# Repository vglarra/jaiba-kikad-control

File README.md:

# jaiba-kicad-control

KiCad project for the Jaiba hexa-drum's control board: three Teensy 4.1s in
sockets — one per hemisphere plus one for the UI — with a velostat **and** a
piezo front-end for every drum sensor, plus five loop-control sensors.

## System overview

```mermaid
graph LR
    R["Right hemisphere Teensy<br/>9 sensors x (velostat + piezo)<br/>USB-MIDI out"]
    L["Left hemisphere Teensy<br/>7 sensors x (velostat + piezo)<br/>+ 5 loop sensors via mux<br/>USB-MIDI out"]
    UI["UI Teensy<br/>ST7796 TFT + XPT2046 touch"]

    R -- "Serial1, crossed<br/>pins 0/1" --> UI
    L -- "Serial3, crossed<br/>pins 14/15" --> UI
```

Every sensor Teensy sends MIDI straight to the host over its own USB port; the
UART links carry calibration commands and live monitoring only. Each sensor
Teensy is a separate USB-MIDI device and the host merges them.

## The 18-analog-input ceiling

This is the constraint the whole layout follows.

A Teensy 4.1 has exactly **18 analog inputs**, and it is a hardware limit, not a
software one: the i.MX RT1062 has 18 ADC-capable pads and Teensy 4.1 breaks all
of them out. Pins 28–37 are *not* analog — the core's `pin_to_channel[]` table
returns `255` for them, and `analogRead()` returns 0.

```
A0  A1  A2  A3  A4  A5  A6  A7  A8  A9  A10 A11 A12 A13 A14 A15 A16 A17
14  15  16  17  18  19  20  21  22  23  24  25  26  27  38  39  40  41
```

Each drum sensor needs **two** analog inputs — one for its velostat layer, one
for its piezo layer — so:

| Board | Sensors | Analog pins | Spare |
|---|---|---|---|
| Right hemisphere | 9 dual-layer | 18/18 | 0 |
| Left hemisphere | 7 dual-layer + 5 loop | 15/18 | 3 |
| UI Teensy | — | 0/18 | 16 |
| **Total** | **16 dual-layer + 5 loop = 21** | | |

The five loop sensors cannot fit alongside the hemisphere sensors: 16 dual-layer
sensors already consume 32 of the two sensor Teensys' 36 analog pins, and the
left Teensy has only **4** spare — one short of five.

So the loop sensors are wired **velostat-only** (they need one pin each, not
two, because nothing needs their attack velocity) and **share a single ADC pin
through a CD74HC4067 16:1 multiplexer** on the left Teensy: `C0`–`C4` are the
loop sensors, `SIG` goes to one analog pin, `S0`–`S3` to four digital pins, and
`EN` is tied to ground so the mux is always enabled. That leaves **11 mux
channels free** for future pads.

**This costs the percussive pads nothing.** The mux is never in their signal
path — they keep dedicated ADC pins — and because the loop sensors leave the
percussive scan entirely, the fast loop actually gets *shorter* (7 pads instead
of the 9 that two dual-layer loop sensors would have made). The loop sensors can
be read on a slow `millis()` cadence since velostat control does not need a
high sample rate.

### Two more things that shape the layout

**The analog pins are lopsided across the two rows.** Fourteen of the eighteen
sit on ROW1 (pins 14–23 and 38–41); only four (24–27) are on ROW2. That is why
each sensor Teensy's 7 ROW1-only sensors are the ones that get dedicated pins,
and why the loop sensors (which need one pin each, not two) were the ones moved
behind the mux.

**Two ADCs.** Pins 26/27 (A12/A13) and 38/39 (A14/A15) are ADC2-only; the other
fourteen are ADC1. `analogRead()` handles the switching transparently, but it
matters if you ever want simultaneous sampling.

## Floorplan

The drum pad cables arrive at the **right-hand edge** of the board, and the three
Teensys' USB sockets point **left**, so the board splits into two regions:

```
   +----------------------------------------------------------+
   |  U_R  [buttons]                       colA         colB  |
   |  U_L  [buttons]   U_MUX             ||    ||      ||   || |
   |  U_UI [TFT]                         ||    ||      ||   || |
   |                                   (8 dual + 3    (8 dual +|
   |                                    loop rows)    2 loops) |
   +----------------------------------------------------------+
```

* **Left** — the three Teensys stacked vertically with their USB sockets facing
  left, each sensor Teensy with its cal/curve buttons below it, plus the mux and
  the TFT header.
* **Right** — every sensor connector, in **two columns of cells whose connectors
  face outward**: 21 connectors at x = 120 mm (11 of them) and x = 152 mm (10).
  The aisle between the columns is what lets a cable reach the inner one.
* **Buses** run vertically at x = 92 mm (3V3) and x = 100 mm (GND), between the
  two regions, where they clear every courtyard on both sides.

A cell's connector sits on the **right** of the cell, which is why
`sensor_cell(..., mirrored=True)` exists: it is a true mirror of the left-facing
variant about the cell's centre line, and mirroring is what keeps the internal
routing crossing-free.

**What this costs.** Gathering the connectors here makes each cell's two runs to
its Teensy long jumpers — roughly 30–130 mm instead of the ~15 mm they were when
the cells sat directly above ROW1. They are wire jumpers either way on a
single-sided board, but it is the main trade of this arrangement: the piezo ADC
node (about 5 kΩ source impedance) now travels the length of the board. If that
shows up as noise on the piezo channels, the fix is to keep the piezo front end
by the Teensy and move only the connector out to the edge.

## Board geometry

* **150 × 260 mm**, two copper layers in KiCad's stackup. Fixed by the enclosure,
  so it is a constraint rather than an outcome. Reaching 150 wide was a re-flow
  of the left region, not of the cell columns: the old layout had ~30 mm of dead
  space between the Teensys and the buses. The extra 20 mm of height went into
  the cell row pitch (25 → 27 mm) and the button cluster.
* Rows are **15.24 mm apart** (0.6"), pin span 58.42 mm, board 60.96 × 17.78 mm.
  (0.7" is the *board width*, not the row pitch — an earlier revision used
  17.78 mm as `ROW_GAP` and the sockets could not line up with a real Teensy.)
* Power buses run the full height at x = 66 mm (3V3) and x = 71 mm (GND).
  Neither bar is tapped by any track or pad — they are hand-soldered jumper
  rails, and the ground connection is the F.Cu pour. The channel they sit in is
  bounded by the wire-pad fan at x = 64.81 on the left and the sensor front-ends
  at 78.79 on the right, so a future move anywhere in 73–78 is clear.
* Mounting holes at 6 mm in from each corner.

## Sensor front-ends

Each sensor is one 4-pin connector (`3V3`, `VELO`, `PIEZO`, `GND`) plus its
divider parts, so a hemisphere's nine sensors are nine identical cells:

**Velostat layer** — the sheet is the top leg, the board's 100 Ω is the bottom:

```
3V3 ── velostat ──┬── VELO  (ADC pin)
                  │
                 100Ω
                  │
                 GND
```

**Piezo layer** — 10k/10k attenuator with a clamp diode:

```
PIEZO ── R1 (10k) ──┬── PSIG  (ADC pin)
                    │
                   R2 (10k)          1N4148
                    │                 │
                   GND      anode ────┴──── cathode → 3V3
```

The diode's **anode** faces the ADC node and its **cathode** faces 3.3 V. Note
that KiCad's `D_DO-35_SOD27_P7.62mm_Horizontal` numbers pad 1 as the *cathode*
— the earlier revision of this board had pad 1 on the ADC node, which
forward-biases the diode for any signal below ~2.6 V and clamps the piezo node
flat instead of protecting it.

## Pin tables (verified)

Read off a real Teensy 4.1, then cross-checked against a published Teensy 4.1
footprint and symbol pair (the two agree exactly). Index 0 is the end nearest
the USB connector.

```
ROW1: 5V, GND, 3V3, 23, 22, 21, 20, 19, 18, 17, 16, 15, 14, 13, GND, 41, 40, 39, 38, 37, 36, 35, 34, 33
ROW2: GND, 0, 1, 2, 3, 4, 5, 6, 7, 8, 9, 10, 11, 12, 3V3, 24, 25, 26, 27, 28, 29, 30, 31, 32
```

The 5 V pin is the pin PJRC calls VIN; there is no VIN pad in either main row.

### Copper sizes for home etching

This board is hand-etched — no solder mask, no plated barrels — so the copper is
deliberately far fatter than a fab would ask for. Three constants in
`jaiba_board_layout.py` drive it, and all three footprint generators read them,
so changing them keeps the library and the board in step:

```python
TRACK_W = 0.8          # signal
BUS_W   = 1.0          # power bus bar
PAD_DIA = 2.2          # every plated through-hole pad
```

What that produces on the finished board:

| feature | size |
|---|---|
| pad diameter, all plated pads | 2.2 mm |
| track width | 0.8 mm signal, 1.0 mm bus |
| **narrowest gap, pad to pad** | **0.34 mm** |
| narrowest gap, track to pad | 1.04 mm |
| narrowest gap, track to track | 1.74 mm |
| smallest annular ring | 0.55 mm |
| mounting holes | 3.2 mm NPTH, unplated (unchanged) |

**The 0.34 mm pad-to-pad gap is the etch limit.** It is not a one-off: it occurs
at every adjacent pair on every 2.54 mm header, which is most of the board. Two
2.2 mm pads on a 2.54 mm grid leave 2.54 − 2.2 = 0.34 mm, and at that pitch **no
track can pass between two pads at all** (2.54 − 2.2 − 0.8 < 0) — which is why
the cell routing goes around pads rather than between them.

That gap is comfortable for toner transfer *if* the toner adheres and you do not
over-etch; it is where a home board will bridge first if anything does. If it
does, change `PAD_DIA` and re-run the three footprint generators:

| `PAD_DIA` | pad-to-pad gap |
|---|---|
| 2.2 mm (current) | 0.34 mm |
| 2.0 mm | 0.54 mm |
| 1.8 mm | 0.74 mm |

The board outline and every part position are unaffected — only the pads change.

### Single-sided copper

The physical build is one copper layer, so nothing can cross anything else in
copper. KiCad has no single-layer stackup (it requires an even count, minimum
two), so the board is 2-layer in KiCad and single-sided is a *manufacturing*
decision: only `F.Cu` is fabricated, and everything the plan lists as a jumper
becomes an insulated wire on the component side.

The generator draws only what can never cross: the bus bars, the short
intra-cell links, the five loop-sensor wipers, and the seven TFT/touch signals
that run straight up from their header to the UI Teensy's ROW2. **57 jumper
links remain** — each channel's runs to its analog pin, every cell's 3V3/GND
taps, the buttons, the UART links, TFT SCK, and the mux's own power and signal
runs. Run **Inspect → DRC** to see them as ratsnest.

## Files

| Path | What it is |
|---|---|
| `jaiba_board_layout.py` | **Source of truth.** Pure-Python placement + net plan, no `pcbnew`. |
| `jaiba-kicad-controlboard.py` | Applies the plan via `pcbnew`; run inside KiCad's Scripting Console. |
| `kicad-control-board/jaiba.pretty/` | Project-local footprint library — self-contained, no KiCad system libs. |
| `kicad-control-board/*.kicad_pcb` | Generated board (150 × 260 mm, 281 footprints, 612 pads). |
| `tools/make_library.py` | Rebuilds `jaiba.pretty/` by lifting footprints out of the board. |
| `tools/make_teensy_footprint.py` | Generates `Teensy_4.1.kicad_mod` from PJRC's published dimensions. |
| `tools/make_module_footprint.py` | Generates `CD74HC4067_Module.kicad_mod` from caliper measurements, plus its 1:1 check sheet. |
| `tools/make_calibration_sheet.py` | Emits `calibration_1to1.svg` — the ruler that proves a print really is 1:1. |
| `tools/make_teensy_fit_gauge.py` | Emits `teensy_fit_gauge.svg` — nominal Teensy pin rows to lay the real part on. |
| `tools/emit_board.py` | Writes the `.kicad_pcb` from the plan **without** KiCad. |
| `tools/route_jumpers.py` | Pre-routes the wire jumpers onto B.Cu as a guide (see below). |
| `tools/check_pour.py` | Measures whether a ground pour would actually connect (see below). |
| `tools/preview_board.py` | Renders the board to an SVG so a floorplan change can be eyeballed without KiCad. |
| `tools/verify_board.py` | DRC-style geometry checker (plan or emitted board). |
| `tools/kicad_sexpr.py` | S-expression reader/writer, quote-preserving. |

## Regenerating the board

**With KiCad** — open the PCB Editor, open **Tools → Scripting Console**:

```python
exec(open(r'/path/to/jaiba-kicad-controlboard.py').read())
```

**Without KiCad** — the same board straight from the plan:

```bash
python3 tools/emit_board.py            # writes kicad-control-board.kicad_pcb
python3 tools/verify_board.py kicad-control-board/kicad-control-board.kicad_pcb
```

**Full rebuild from scratch** — if `jaiba.pretty/` is ever missing, this
regenerates every footprint before the board. Order matters: the library has to
exist before `emit_board.py` can read it.

```bash
python3 tools/make_library.py           # passives, lifted out of the board
python3 tools/make_teensy_footprint.py  # Teensy 4.1, from PJRC dimensions
python3 tools/make_module_footprint.py  # CD74HC4067 module, from caliper measurements
python3 tools/emit_board.py
python3 tools/route_jumpers.py          # optional: B.Cu jumper guide
python3 tools/verify_board.py kicad-control-board/kicad-control-board.kicad_pcb
```

`verify_board.py` checks that no pad or courtyard leaves the outline, no two
pads overlap, no courtyards collide, and no track breaks clearance from another
net, a pad, or a mounting hole. A clean run prints `RESULT: clean`.

**Footprint library.** `jaiba.pretty/` is committed and self-contained, so
neither route needs KiCad's system libraries or a configured install path.
`make_library.py` only needs re-running if you change the passives; it lifts
their geometry out of a board that KiCad wrote. `make_teensy_footprint.py`
generates the Teensy footprint from PJRC's published dimensions, and
`make_module_footprint.py` generates the mux module footprint from your caliper
measurements — it prints a 1:1 SVG sheet alongside, for checking against the
real board on paper.

**Format version.** The emitted board declares KiCad 9's format
(`20241229`). KiCad 9 and 10 both open it; a newer KiCad will offer to upgrade
it in place. The stackup, design rules and plot parameters in
`tools/emit_board.py`'s `BOARD_TEMPLATE` are captured verbatim from a
KiCad-written board — edit them there rather than by hand in the `.kicad_pcb`,
which is regenerated.

## Drum-cable solder pads

The drum cable takes all the movement, so each of its four lands on its own bare
copper pad rather than only on a 2.2 mm through-hole pad. **74 pads** — four per
dual-layer cell (3V3, VELO, PRAW, GND) and two per loop cell.

They are `SolderPad_1x01`: an **8.0 × 2.0 mm rectangle of exposed copper**
(`F.Cu` + `F.Mask` only — no paste layer, because there is no stencil), sitting
just outboard of each cell's connector and fed by a straight horizontal stub
from its pin. Per connection that is 3.8 mm² of through-hole pad plus 16.0 mm² of
rectangle — **19.8 mm², 5.2× the round pad alone** — and an **8 mm run of copper**
to solder the wire along rather than one small pad.

Two constraints shaped it:

* **They could not go beside the connector in X.** The passives are ~1 mm to its
  left and the cell edge 0.8 mm to its right, so every vertical channel inside
  the cell is blocked. Outboard of the connector is the only clear space — which
  also happens to be the side the drum cable arrives from.
* **2.0 mm tall, not more.** Adjacent pins are 2.54 mm apart, so the height is
  capped at ~2.34 mm before neighbouring courtyards touch. The 2.4 mm courtyard
  leaves 0.14 mm between them.
* **8 mm is the length limit in practice** — and only because of where the pads
  land, not a rule. At 8 mm the rightmost pad ends 9.5 mm short of the edge.

Being surface-mount, these add **no holes** — the drill count is unchanged.

The 8 mm length pushed the loop cells' jumper pads out of the strip they shared
with the drum pads, so those moved below (row pitch 8 → 11 mm) and column B moved
110 → 114 mm to keep the aisle between the columns. The left region absorbed the
rest of the squeeze to 150 mm wide, leaving both cell columns where they are.

## Wire landing pads

Soldering a jumper onto a pin that already holds a socket or a module pin puts
**two joints in one hole** and pours heat into the part. So every end of every
jumper gets a pad of its own, reached by a short F.Cu stub. **100 of them:**

| where | pads | why |
|---|---|---|
| beside the Teensys | 50 | 22 right, 23 left (it also carries the mux lines), 5 UI |
| beside the mux module | 13 | `C0`–`C4`, `SIG`, `S0`–`S3`, `EN`, `VCC`, `GND` |
| in the sensor cells | 32 | `VELO` and `PSIG` for each of the 16 dual-layer sensors |
| in the loop cells | 5 | `VELO` for each |

TFT pins 6–12 have none: they are already drawn in copper to the header.

**Beside the Teensys and the mux** the pads step *diagonally* — each one further
out from the pin row and further along than the last — so the wires comb out
instead of bunching at 2.54 mm pitch. Stubs cannot cross, provably: a stub always
ends left of where the next one starts (`i × 1.15 < 2.54 × (i+1)`). Consecutive
pads land about 3.9 mm apart. The mux's channel inputs fan up and its control
pins fan down, so the module's two rows don't fight for the same space.

**In the sensor cells** the two pads go on the sides their nodes already live on,
because putting both on the right makes the two routes *topologically cross* —
no planar routing can fix that:

```
        R_VELO                                          J_PAD  (3V3 VELO PRAW GND)
   ┌──────────────┐                                        │
   │   ○ VELO     │  <- velostat pad, in the free band      │
   ├──────────────┤     between R_VELO and R1               │
   │   R1    R2   │                                         │
   │              │                                         │
   │   D          │  ○ PSIG  <- piezo pad, crossed on y=18.5 │
   └──────────────┘
```

The cal/curve buttons moved to the right-hand side of each Teensy for this: their
pads were landing *inside* the switches. Being off to the side also puts them
somewhere a finger can reach.

The B.Cu jumper guide aims at these pads rather than at component leads, which is
where the wire physically goes.

## The B.Cu jumper guide

The board is single-sided, so the ~60 connections the generator leaves unrouted
become insulated wire jumpers on the component side. KiCad draws those as
straight ratsnest lines, which at this count is an unreadable spider web.

`tools/route_jumpers.py` lays a plausible *path* for each one on **B.Cu**. That
layer is not fabricated, so it is free to use as a map, and it is a faithful
model:

* every jumper ends on a through-hole pad, and THT pads exist on all copper
  layers, so **no vias are ever needed**;
* a B.Cu track cannot clash with the F.Cu copper — which is exactly right, since
  the real wires are insulated and cross traces freely;
* B.Cu coordinates map 1:1 onto the component side, so what you see in the normal
  top view is where the wire physically goes.

Routes are orthogonal paths on a 0.635 mm lattice, avoiding pads of other nets,
mounting holes and the board edge. **They are allowed to cross each other** —
forbidding that is not a real constraint for insulated wire, and enforcing it
strangled the few corridors into the Teensys. So the guide contains many
crossings on purpose.

> **When plotting for etching, select `F.Cu` only.** B.Cu now contains copper and
> must never be made. `kicad-cli pcb export gerbers` would export both.

The verifier knows about layers: it checks F.Cu strictly, and reports B.Cu
crossings as a count rather than as shorts. KiCad's own DRC will flag them —
exclude B.Cu, or just remember what that layer is.

## A note on file formatting

`emit_board.py` refuses to write a board whose quoting KiCad would reject. The
specific trap: KiCad's parser accepts a bare *symbol* almost anywhere — unquoted
`(layer F.Cu)` and bare uuids load fine — but a value that tokenises as a
**number** where it wants a symbol is fatal. `(generator_version 9.0)` produces
exactly one error, naming a line number and nothing else:

```
Expecting 'symbol' in '...kicad-control-board.kicad_pcb', line 27117, offset 22
```

The lint walks the tree before writing and reports the path to any such value,
so this surfaces as a build error instead of a KiCad load failure.

Worth knowing: `make_library.py` lifts the passive footprints **out of the
generated board**, so its formatting style feeds back into the library and then
into the next generation. That is self-correcting now that the emitter writes
canonically, but if the board file is ever hand-edited into a non-canonical
style, re-running the chain will propagate it.

## Encoder expansion headers

The UI Teensy has **26 free digital pins** broken out on three headers, so a knob
panel can be added without soldering onto a socket pin:

| | pins | carries |
|---|---|---|
| `J_ENC_A` | 10 | **GND, 3V3**, then Teensy 23, 22, 21, 20, 19, 18, 17, 16 |
| `J_ENC_B` | 9 | Teensy 41, 40, 39, 38, 37, 36, 35, 34, 33 |
| `J_ENC_C` | 9 | Teensy 24, 25, 26, 27, 28, 29, 30, 31, 32 |

All 16 analog-capable pins (16–27, 38–41) are included, plus 10 digital-only ones.
`J_ENC_A` carries the power, taken from the Teensy's own ROW1 GND and 3V3 pins, so
no bus has to be tapped — the encoder commons can share its GND.

**Why three headers and not one.** Each Teensy pin row is a wall: a track cannot
pass between two 2.2 mm pads on a 2.54 mm pitch, so nothing can reach ROW1 from
below. Each header therefore sits on the side of the row it serves, directly
above or below it, and **every trace is a straight vertical** — pin for pin, no
crossings, no jumpers, no vias.

`J_ENC_A` sits 5.5 mm higher than `J_ENC_B` to squeeze between two obstacles: the
mux's channel extension pads below it and the UART landing pad for pin 15 above.
The header courtyard is ±1.77 (it inherits the 1×02 shell), which is what makes
that window so narrow.

### If you use potentiometers instead

Encoders are digital and use no ADC. If you switch to pots, the same headers work
— each pot wiper goes to one pin, 3V3 and GND come from `J_ENC_A`. **16 of the 26
pins are analog-capable**, so there is no need for another multiplexer: the left
Teensy's CD74HC4067 also still has **11 spare channels**, read over the UART.

## The electrostatic shield

The copper fill on F.Cu is tied to **GND** and acts as a coplanar shield and
guard around the high-impedance piezo nodes.

**It has to be grounded.** Floating copper is the opposite of a shield: it
re-radiates and capacitively couples noise onto the very nodes it sits beside.
So the zone carries the ground net and no fragment may be left floating —
`island_removal_mode 2` makes KiCad drop any that reaches no ground pad.

The fragmentation that rules the fill out as a ground *return path* is fine for
a shield, because each piece only has to be grounded, not joined to the others:

```
SHIELD : 15 of 146 pour regions reach ground
         292.81 cm2 of useful shield      (75% of the board)
         4.52 cm2 floating -> removed     (1.2%, negligible)
```

Ground reaches each region through a thermal spoke from a ground pad, and those
pads are being wired anyway — so the shield needs no extra connections. It also
does some of that wiring for you: with the shield, ground forms 15 groups instead
of 31, so relying on it would cut the ground wires from 31 to about 14. That is
still the unpredictable road, so the board is built for the 31.

Roughly three quarters of the board is also bare laminate, and every square
millimetre of it is copper the etchant has to remove — so the shield shortens the
etch as a side effect. Settings live at the top of `tools/emit_board.py`:
clearance 0.40 mm (never tighter than the board's own 0.34 mm minimum feature),
min thickness 0.50 mm so no unetchable slivers are left.

> **The board file is written UNFILLED.** KiCad computes the fill itself, so
> **press B (Fill All Zones) before plotting**, or F.Cu plots with no fill at
> all. `verify_board.py` says so every time it runs.
>
> The committed `.kicad_pcb` *does* carry a filled pour, and a stored fill goes
> stale the moment geometry moves: the polygons still hold the clearance slot
> around wherever a track used to be. A stale fill around a *foreign* net's
> copper is a short, not a gap — which is exactly why the B press is not
> optional after any layout edit.

### What it is not

A **coplanar** shield lies on the same layer as the traces, so it cannot block
fields arriving from directly above them. It guards — it intercepts surface
leakage and shrinks the pickup area around the nodes — but it is not a true
planar shield.

That needs a ground plane on **B.Cu**, which means a two-layer board. It would
also eliminate the ground wiring and the whole jumper guide, because the routing
could move to the second layer. That is a different board, not a tweak.

The shield does add capacitance from the piezo node to ground. At the node's
5 kΩ (10k ‖ 10k) and on the order of 20 pF of coupling that is a pole near
1.6 MHz — three decades above audio, so it costs nothing in the signal band.

### Why it is not a ground pour

A pour looks like the obvious way to remove the ground jumpers. On a
**single-sided** board it does not work, and `tools/check_pour.py` measures why
rather than asserting it:

```
pour-able area : 261.4 cm2 of 390.0 cm2 (66.9%)
pour regions   : 367  (largest 12710 mm2)
thermal spokes : 263 pad-to-region links
!! ground is SPLIT into 33 separate pieces
   largest group: 40 of 92 ground pads
```

Every signal trace is a wall through the plane, and 596 of them partition it
whatever the clearance. Modelling thermal spokes matters a great deal — a pad
does not have to sit *in* the pour, a spoke crosses its clearance ring, and on a
2.54 mm pitch with 2.2 mm pads that is the only way most pads ever connect. It
took the count from 73 fragments down to 33, and no further.

So a pour would have replaced 63 ground wires with roughly 32, **unpredictably**:
there is no way to tell by eye which pads are already joined, and the fragments
form parallel ground paths right beside the high-impedance piezo nodes.

## Cutting the ground wiring in copper instead

Each dual-layer cell has **three** ground points — the connector's GND (with its
drum pad already stubbed to it), the piezo divider's GND, and the velostat
pulldown's GND. A short F.Cu run joins all three, going the long way round
because the pulldown's GND pad sits behind the piezo node with the psig feed
running down that same column:

```
RV.2 ─┐
      └─ x=3.4 down ── y=14 across ── R2.2 ── y=16.5 ── J.4
```

That takes ground from **63 wire connections to 31**. `3V3` is now the largest
remaining item at **42**, because the diode's 3V3 pad at (9.46, 21) sits in a
pocket: the psig feed runs across the cell at y=18.50 above it, the cell ends
40 mm... at y=22.25 below it, and the drum stubs wall off the right-hand side.
Joining it needs a cell re-layout rather than another trace.

## Open items

- [ ] **Firmware split.** `SensorFirmware_Arduino.ino` still runs 6 velostat
      (A0–A5) + 6 piezo (A6–A11) on a *single* sensor Teensy. This board has two
      hemisphere Teensys — 9 dual-layer sensors on the right, 7 on the left —
      so the sensor firmware needs a per-hemisphere variant (or a board-ID
      offset).
- [ ] **Loop-sensor firmware.** The left Teensy now drives the CD74HC4067's
      four select lines and reads `SIG`; the loop pads are velostat-only, so the
      per-pad piezo path (`analogRead(s.piezoPin)`, and `piezoPins[]` at setup)
      needs a "this pad has no piezo" guard. Read them on a slow `millis()`
      cadence, not in the percussive scan.
- [ ] **UI firmware only reads `Serial1`.** `Serial3` appears nowhere in either
      firmware, so the left-hemisphere link is dead copper until the UI reads
      it and merges two sensor streams.
- [x] **Printer measured and compensated — DONE.** The paper check is now
      trustworthy. Through the browser SVG path the bench enlarges by **1.3266**
      (the classic 96-vs-72 dpi mismatch): the sheet's own 100 mm bar came off at
      134 mm, then 99 mm once over-corrected at 1.34, and at **1.3266 it reads
      exactly 100 mm with the Teensy pin span matching a real header.** All three
      1:1 sheets are generated at that factor and each has since been confirmed on
      its *own* 100 mm bar — `jaiba.pretty/calibration_1to1.svg`,
      `jaiba.pretty/teensy_fit_gauge.svg`, and the module's
      `jaiba.pretty/CD74HC4067_Module_1to1_printfix.svg`:
      `python3 tools/make_calibration_sheet.py 1.3266`.
      Notes that matter for the next person:
      * The factor is the *pipeline's* own ratio (printed/true), not the
        correction — the emitter divides by it. Get the direction wrong and the
        error doubles instead of cancelling.
      * The board via KiCad → PDF → viewer is a **different** pipeline that
        *shrinks* (measured 0.9957 from a 58.42 → 58.15 mm row). Print the check
        sheet and the board through the same one, and re-measure the bar rather
        than reusing a factor.
      * 1.3266 is within 0.5 % of the `PRINTER_SCALE = 1.32` that
        `tools/make_module_footprint.py` carried from a 50 mm bar. Same effect,
        two independent measurements; the longer bar wins, and the tool now uses
        1.3266 with a 100 mm bar so the two cannot drift apart again.
      * Every sheet carries its own bar for a reason: a wrong factor looks
        perfect. Re-measure it on each new print rather than trusting the file.
- [x] **Teensy pad span — RESOLVED, no change made.** The real 24-pin header
      measures 58.40–58.50 mm and the design is 58.42 mm (2.54 mm pitch × 23):
      they agree, and once the print was compensated the row matched the real
      header exactly. Every apparent discrepancy along the way (59.2, 59.3) was
      the paper or the caliper convention — a standard 0.64 mm post row measures
      58.42 mm centre-to-centre but 59.06 mm outer-edge-to-outer-edge. Widening
      the pads to chase a print was the wrong fix and would have produced a
      footprint a real Teensy no longer fits (a 58.90 mm span implies a 2.561 mm
      pitch), because `TEENSY_PITCH` also drives the UART and mux landing-pad
      fans and the pitch-aligned TFT header. Fix the paper, not the copper.
- [ ] **Verify the module footprint before ordering.** `CD74HC4067_Module`
      is generated from caliper measurements; the two pin spans were confirmed
      at exactly 38.10 mm and 17.78 mm, but `row_spacing` (14.9 mm measured, vs
      the 15.24 mm 0.1″-grid value) is still unconfirmed. The blocking
      precondition is now cleared: `jaiba.pretty/CD74HC4067_Module_1to1_printfix.svg`
      is generated at the confirmed 1.3266 factor and **its own 100 mm bar has
      been measured at exactly 100 mm with calipers**, so a reading taken off that
      sheet means something. What remains is the physical test — lay the real
      module on the sheet and check every pin drops into a hole. If it does,
      `row_spacing = 14.9` is real and the footprint ships as built; if the rows
      sit wide or narrow, it is one constant in `tools/make_module_footprint.py`
      (the 0.1″-grid value is 15.24). Either way the board outline is unaffected.
      Note this is the last geometry question in the project that paper can
      settle, so it is worth doing before the sheet goes stale.
- [ ] **There is no schematic.** `kicad-control-board.kicad_sch` is empty, so
      nets exist only in the PCB, there is no ERC, and "Update PCB from
      Schematic" would wipe the design.
- [ ] **Reconsider single-sided.** 37 analog channels plus the mux is a lot of
      wire jumpers; a normal 2-layer fab would route nearly all of them in
      copper.
- [ ] Confirm the Teensy footprint's row assignment (ROW1 at y = −7.62) against
      a real Teensy in KiCad's footprint viewer before ordering.

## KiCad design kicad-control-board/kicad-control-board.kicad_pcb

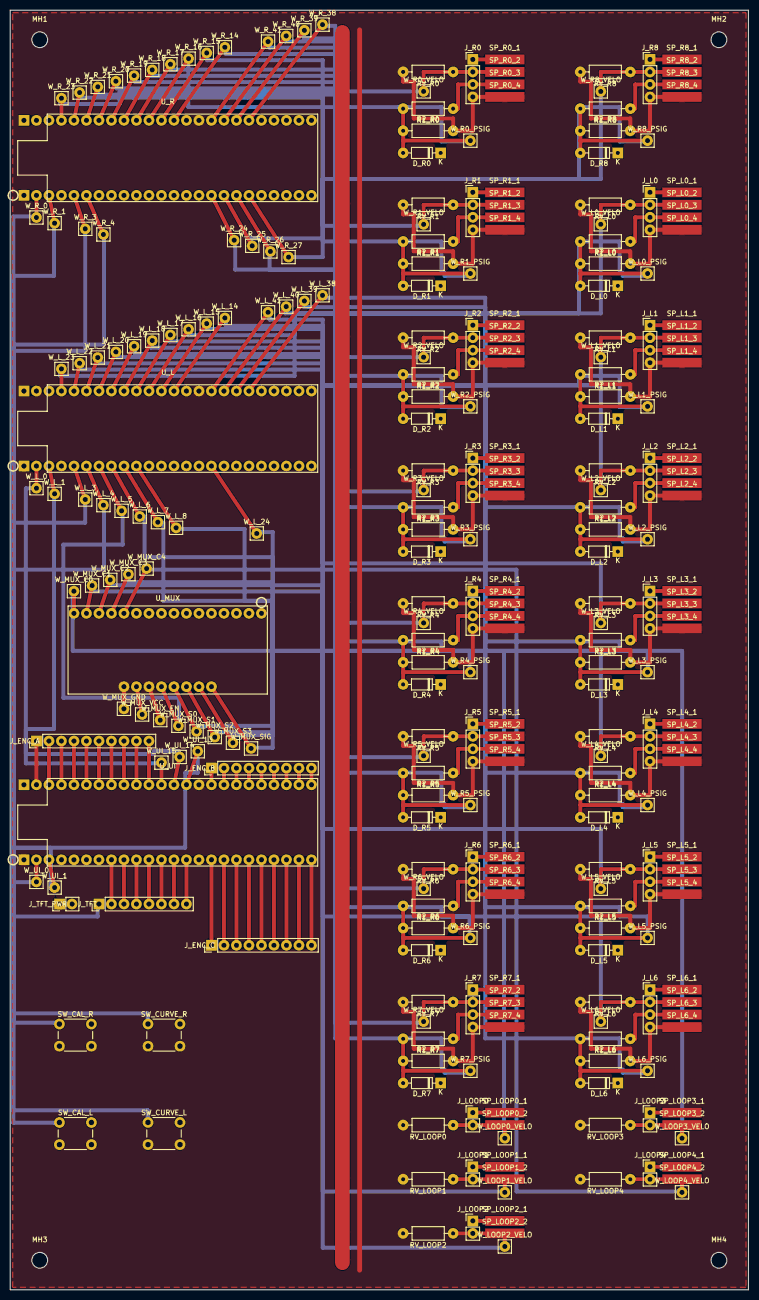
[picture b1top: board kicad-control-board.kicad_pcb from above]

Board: 2 copper layers, 150.0 x 260.0 mm, 281 parts (0 on the bottom side), 102 nets.

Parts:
D_L0, D_L1, D_L2, D_L3, D_L4, D_L5, D_L6: 1N4148; D_DO-35_SOD27_P7.62mm_Horizontal
D_R0, D_R1, D_R2, D_R3, D_R4, D_R5, D_R6, D_R7, D_R8: 1N4148; D_DO-35_SOD27_P7.62mm_Horizontal
J_ENC_A: Conn_01x10; PinHeader_1x10_P2.54mm_Vertical
J_ENC_B: Conn_01x09; PinHeader_1x09_P2.54mm_Vertical
J_ENC_C: Conn_01x09; PinHeader_1x09_P2.54mm_Vertical
J_L0, J_L1, J_L2, J_L3, J_L4, J_L5, J_L6: Conn_01x04; PinHeader_1x04_P2.54mm_Vertical
J_LOOP0, J_LOOP1, J_LOOP2, J_LOOP3, J_LOOP4: Conn_01x02; PinHeader_1x02_P2.54mm_Vertical
J_R0, J_R1, J_R2, J_R3, J_R4, J_R5, J_R6, J_R7, J_R8: Conn_01x04; PinHeader_1x04_P2.54mm_Vertical
J_TFT: Conn_01x08; PinHeader_1x08_P2.54mm_Vertical
J_TFT_PWR: Conn_01x02; PinHeader_1x02_P2.54mm_Vertical
MH1, MH2, MH3, MH4: MountingHole; MountingHole_3.2mm_M3
R1_L0, R1_L1, R1_L2, R1_L3, R1_L4, R1_L5, R1_L6, R1_R0, R1_R1, R1_R2, R1_R3, R1_R4, R1_R5, R1_R6, R1_R7, R1_R8, R2_L0, R2_L1, R2_L2, R2_L3, R2_L4, R2_L5, R2_L6, R2_R0, R2_R1, R2_R2, R2_R3, R2_R4, R2_R5, R2_R6, R2_R7, R2_R8: 10k; R_Axial_DIN0207_L6.3mm_D2.5mm_P10.16mm_Horizontal
RV_L0, RV_L1, RV_L2, RV_L3, RV_L4, RV_L5, RV_L6: 100; R_Axial_DIN0207_L6.3mm_D2.5mm_P10.16mm_Horizontal
RV_LOOP0, RV_LOOP1, RV_LOOP2, RV_LOOP3, RV_LOOP4: 100; R_Axial_DIN0207_L6.3mm_D2.5mm_P10.16mm_Horizontal
RV_R0, RV_R1, RV_R2, RV_R3, RV_R4, RV_R5, RV_R6, RV_R7, RV_R8: 100; R_Axial_DIN0207_L6.3mm_D2.5mm_P10.16mm_Horizontal
SP_L0_1, SP_L0_2, SP_L0_3, SP_L0_4, SP_L1_1, SP_L1_2, SP_L1_3, SP_L1_4, SP_L2_1, SP_L2_2, SP_L2_3, SP_L2_4, SP_L3_1, SP_L3_2, SP_L3_3, SP_L3_4, SP_L4_1, SP_L4_2, SP_L4_3, SP_L4_4, SP_L5_1, SP_L5_2, SP_L5_3, SP_L5_4, SP_L6_1, SP_L6_2, SP_L6_3, SP_L6_4: SolderPad; SolderPad_1x01
SP_LOOP0_1, SP_LOOP0_2, SP_LOOP1_1, SP_LOOP1_2, SP_LOOP2_1, SP_LOOP2_2, SP_LOOP3_1, SP_LOOP3_2, SP_LOOP4_1, SP_LOOP4_2: SolderPad; SolderPad_1x01
SP_R0_1, SP_R0_2, SP_R0_3, SP_R0_4, SP_R1_1, SP_R1_2, SP_R1_3, SP_R1_4, SP_R2_1, SP_R2_2, SP_R2_3, SP_R2_4, SP_R3_1, SP_R3_2, SP_R3_3, SP_R3_4, SP_R4_1, SP_R4_2, SP_R4_3, SP_R4_4, SP_R5_1, SP_R5_2, SP_R5_3, SP_R5_4, SP_R6_1, SP_R6_2, SP_R6_3, SP_R6_4, SP_R7_1, SP_R7_2, SP_R7_3, SP_R7_4, SP_R8_1, SP_R8_2, SP_R8_3, SP_R8_4: SolderPad; SolderPad_1x01
SW_CAL_L: SW_PUSH; SW_PUSH_6mm
SW_CAL_R: SW_PUSH; SW_PUSH_6mm
SW_CURVE_L: SW_PUSH; SW_PUSH_6mm
SW_CURVE_R: SW_PUSH; SW_PUSH_6mm
U_L: Teensy4.1; Teensy_4.1
U_MUX: CD74HC4067; CD74HC4067_Module
U_R: Teensy4.1; Teensy_4.1
U_UI: Teensy4.1; Teensy_4.1
W_L0_PSIG, W_L0_VELO, W_L1_PSIG, W_L1_VELO, W_L2_PSIG, W_L2_VELO, W_L3_PSIG, W_L3_VELO, W_L4_PSIG, W_L4_VELO, W_L5_PSIG, W_L5_VELO, W_L6_PSIG, W_L6_VELO: WirePad; WirePad_1x01
W_LOOP0_VELO, W_LOOP1_VELO, W_LOOP2_VELO, W_LOOP3_VELO, W_LOOP4_VELO: WirePad; WirePad_1x01
W_L_0, W_L_1, W_L_3, W_L_4, W_L_5, W_L_6, W_L_7, W_L_8, W_L_14, W_L_15, W_L_16, W_L_17, W_L_18, W_L_19, W_L_20, W_L_21, W_L_22, W_L_23, W_L_24, W_L_38, W_L_39, W_L_40, W_L_41: WirePad; WirePad_1x01
W_MUX_C0, W_MUX_C1, W_MUX_C2, W_MUX_C3, W_MUX_C4: WirePad; WirePad_1x01
W_MUX_EN: WirePad; WirePad_1x01
W_MUX_GND: WirePad; WirePad_1x01
W_MUX_S0, W_MUX_S1, W_MUX_S2, W_MUX_S3: WirePad; WirePad_1x01
W_MUX_SIG: WirePad; WirePad_1x01
W_MUX_VCC: WirePad; WirePad_1x01
W_R0_PSIG, W_R0_VELO, W_R1_PSIG, W_R1_VELO, W_R2_PSIG, W_R2_VELO, W_R3_PSIG, W_R3_VELO, W_R4_PSIG, W_R4_VELO, W_R5_PSIG, W_R5_VELO, W_R6_PSIG, W_R6_VELO, W_R7_PSIG, W_R7_VELO, W_R8_PSIG, W_R8_VELO: WirePad; WirePad_1x01
W_R_0, W_R_1, W_R_3, W_R_4, W_R_14, W_R_15, W_R_16, W_R_17, W_R_18, W_R_19, W_R_20, W_R_21, W_R_22, W_R_23, W_R_24, W_R_25, W_R_26, W_R_27, W_R_38, W_R_39, W_R_40, W_R_41: WirePad; WirePad_1x01
W_UI_0, W_UI_1, W_UI_13, W_UI_14, W_UI_15: WirePad; WirePad_1x01

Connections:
3V3: D_L0.1, D_L1.1, D_L2.1, D_L3.1, D_L4.1, D_L5.1, D_L6.1, D_R0.1, D_R1.1, D_R2.1, D_R3.1, D_R4.1, D_R5.1, D_R6.1, D_R7.1, D_R8.1, J_ENC_A.2, J_L0.1, J_L1.1, J_L2.1, J_L3.1, J_L4.1, J_L5.1, J_L6.1, J_LOOP0.1, J_LOOP1.1, J_LOOP2.1, J_LOOP3.1, J_LOOP4.1, J_R0.1, J_R1.1, J_R2.1, J_R3.1, J_R4.1, J_R5.1, J_R6.1, J_R7.1, J_R8.1, J_TFT_PWR.2, SP_L0_1.1, SP_L1_1.1, SP_L2_1.1, SP_L3_1.1, SP_L4_1.1, SP_L5_1.1, SP_L6_1.1, SP_LOOP0_1.1, SP_LOOP1_1.1, SP_LOOP2_1.1, SP_LOOP3_1.1, SP_LOOP4_1.1, SP_R0_1.1, SP_R1_1.1, SP_R2_1.1, SP_R3_1.1, SP_R4_1.1, SP_R5_1.1, SP_R6_1.1, SP_R7_1.1, SP_R8_1.1, U_L.3V3, U_MUX.VCC, U_R.3V3, U_UI.3V3, W_MUX_VCC.1
BTN_CAL_L: SW_CAL_L.1, U_L.3, W_L_3.1
BTN_CAL_R: SW_CAL_R.1, U_R.3, W_R_3.1
BTN_CURVE_L: SW_CURVE_L.1, U_L.4, W_L_4.1
BTN_CURVE_R: SW_CURVE_R.1, U_R.4, W_R_4.1
GND: J_ENC_A.1, J_L0.4, J_L1.4, J_L2.4, J_L3.4, J_L4.4, J_L5.4, J_L6.4, J_R0.4, J_R1.4, J_R2.4, J_R3.4, J_R4.4, J_R5.4, J_R6.4, J_R7.4, J_R8.4, J_TFT_PWR.1, R2_L0.2, R2_L1.2, R2_L2.2, R2_L3.2, R2_L4.2, R2_L5.2, R2_L6.2, R2_R0.2, R2_R1.2, R2_R2.2, R2_R3.2, R2_R4.2, R2_R5.2, R2_R6.2, R2_R7.2, R2_R8.2, RV_L0.2, RV_L1.2, RV_L2.2, RV_L3.2, RV_L4.2, RV_L5.2, RV_L6.2, RV_LOOP0.2, RV_LOOP1.2, RV_LOOP2.2, RV_LOOP3.2, RV_LOOP4.2, RV_R0.2, RV_R1.2, RV_R2.2, RV_R3.2, RV_R4.2, RV_R5.2, RV_R6.2, RV_R7.2, RV_R8.2, SP_L0_4.1, SP_L1_4.1, SP_L2_4.1, SP_L3_4.1, SP_L4_4.1, SP_L5_4.1, SP_L6_4.1, SP_R0_4.1, SP_R1_4.1, SP_R2_4.1, SP_R3_4.1, SP_R4_4.1, SP_R5_4.1, SP_R6_4.1, SP_R7_4.1, SP_R8_4.1, SW_CAL_L.2, SW_CAL_R.2, SW_CURVE_L.2, SW_CURVE_R.2, U_L.GND, U_MUX.EN, U_MUX.GND, U_R.GND, U_UI.GND, W_MUX_EN.1, W_MUX_GND.1
LOOP_VELO0: J_LOOP0.2, RV_LOOP0.1, SP_LOOP0_2.1, U_MUX.C0, W_LOOP0_VELO.1, W_MUX_C0.1
LOOP_VELO1: J_LOOP1.2, RV_LOOP1.1, SP_LOOP1_2.1, U_MUX.C1, W_LOOP1_VELO.1, W_MUX_C1.1
LOOP_VELO2: J_LOOP2.2, RV_LOOP2.1, SP_LOOP2_2.1, U_MUX.C2, W_LOOP2_VELO.1, W_MUX_C2.1
LOOP_VELO3: J_LOOP3.2, RV_LOOP3.1, SP_LOOP3_2.1, U_MUX.C3, W_LOOP3_VELO.1, W_MUX_C3.1
LOOP_VELO4: J_LOOP4.2, RV_LOOP4.1, SP_LOOP4_2.1, U_MUX.C4, W_LOOP4_VELO.1, W_MUX_C4.1
L_PRAW0: J_L0.3, R1_L0.1, SP_L0_3.1
L_PRAW1: J_L1.3, R1_L1.1, SP_L1_3.1
L_PRAW2: J_L2.3, R1_L2.1, SP_L2_3.1
L_PRAW3: J_L3.3, R1_L3.1, SP_L3_3.1
L_PRAW4: J_L4.3, R1_L4.1, SP_L4_3.1
L_PRAW5: J_L5.3, R1_L5.1, SP_L5_3.1
L_PRAW6: J_L6.3, R1_L6.1, SP_L6_3.1
L_PSIG0: D_L0.2, R1_L0.2, R2_L0.1, U_L.16, W_L0_PSIG.1, W_L_16.1
L_PSIG1: D_L1.2, R1_L1.2, R2_L1.1, U_L.15, W_L1_PSIG.1, W_L_15.1
L_PSIG2: D_L2.2, R1_L2.2, R2_L2.1, U_L.14, W_L2_PSIG.1, W_L_14.1
L_PSIG3: D_L3.2, R1_L3.2, R2_L3.1, U_L.41, W_L3_PSIG.1, W_L_41.1
L_PSIG4: D_L4.2, R1_L4.2, R2_L4.1, U_L.40, W_L4_PSIG.1, W_L_40.1
L_PSIG5: D_L5.2, R1_L5.2, R2_L5.1, U_L.39, W_L5_PSIG.1, W_L_39.1
L_PSIG6: D_L6.2, R1_L6.2, R2_L6.1, U_L.38, W_L6_PSIG.1, W_L_38.1
L_VELO0: J_L0.2, RV_L0.1, SP_L0_2.1, U_L.23, W_L0_VELO.1, W_L_23.1
L_VELO1: J_L1.2, RV_L1.1, SP_L1_2.1, U_L.22, W_L1_VELO.1, W_L_22.1
L_VELO2: J_L2.2, RV_L2.1, SP_L2_2.1, U_L.21, W_L2_VELO.1, W_L_21.1
L_VELO3: J_L3.2, RV_L3.1, SP_L3_2.1, U_L.20, W_L3_VELO.1, W_L_20.1
L_VELO4: J_L4.2, RV_L4.1, SP_L4_2.1, U_L.19, W_L4_VELO.1, W_L_19.1
L_VELO5: J_L5.2, RV_L5.1, SP_L5_2.1, U_L.18, W_L5_VELO.1, W_L_18.1
L_VELO6: J_L6.2, RV_L6.1, SP_L6_2.1, U_L.17, W_L6_VELO.1, W_L_17.1
MUX_S0: U_L.5, U_MUX.S0, W_L_5.1, W_MUX_S0.1
MUX_S1: U_L.6, U_MUX.S1, W_L_6.1, W_MUX_S1.1
MUX_S2: U_L.7, U_MUX.S2, W_L_7.1, W_MUX_S2.1
MUX_S3: U_L.8, U_MUX.S3, W_L_8.1, W_MUX_S3.1
MUX_SIG: U_L.24, U_MUX.SIG, W_L_24.1, W_MUX_SIG.1
R_PRAW0: J_R0.3, R1_R0.1, SP_R0_3.1
R_PRAW1: J_R1.3, R1_R1.1, SP_R1_3.1
R_PRAW2: J_R2.3, R1_R2.1, SP_R2_3.1
R_PRAW3: J_R3.3, R1_R3.1, SP_R3_3.1
R_PRAW4: J_R4.3, R1_R4.1, SP_R4_3.1
R_PRAW5: J_R5.3, R1_R5.1, SP_R5_3.1
R_PRAW6: J_R6.3, R1_R6.1, SP_R6_3.1
R_PRAW7: J_R7.3, R1_R7.1, SP_R7_3.1
R_PRAW8: J_R8.3, R1_R8.1, SP_R8_3.1
R_PSIG0: D_R0.2, R1_R0.2, R2_R0.1, U_R.16, W_R0_PSIG.1, W_R_16.1
R_PSIG1: D_R1.2, R1_R1.2, R2_R1.1, U_R.15, W_R1_PSIG.1, W_R_15.1
R_PSIG2: D_R2.2, R1_R2.2, R2_R2.1, U_R.14, W_R2_PSIG.1, W_R_14.1
R_PSIG3: D_R3.2, R1_R3.2, R2_R3.1, U_R.41, W_R3_PSIG.1, W_R_41.1
R_PSIG4: D_R4.2, R1_R4.2, R2_R4.1, U_R.40, W_R4_PSIG.1, W_R_40.1
R_PSIG5: D_R5.2, R1_R5.2, R2_R5.1, U_R.39, W_R5_PSIG.1, W_R_39.1
R_PSIG6: D_R6.2, R1_R6.2, R2_R6.1, U_R.38, W_R6_PSIG.1, W_R_38.1
R_PSIG7: D_R7.2, R1_R7.2, R2_R7.1, U_R.26, W_R7_PSIG.1, W_R_26.1
R_PSIG8: D_R8.2, R1_R8.2, R2_R8.1, U_R.27, W_R8_PSIG.1, W_R_27.1
R_VELO0: J_R0.2, RV_R0.1, SP_R0_2.1, U_R.23, W_R0_VELO.1, W_R_23.1
R_VELO1: J_R1.2, RV_R1.1, SP_R1_2.1, U_R.22, W_R1_VELO.1, W_R_22.1
R_VELO2: J_R2.2, RV_R2.1, SP_R2_2.1, U_R.21, W_R2_VELO.1, W_R_21.1
R_VELO3: J_R3.2, RV_R3.1, SP_R3_2.1, U_R.20, W_R3_VELO.1, W_R_20.1
R_VELO4: J_R4.2, RV_R4.1, SP_R4_2.1, U_R.19, W_R4_VELO.1, W_R_19.1
R_VELO5: J_R5.2, RV_R5.1, SP_R5_2.1, U_R.18, W_R5_VELO.1, W_R_18.1
R_VELO6: J_R6.2, RV_R6.1, SP_R6_2.1, U_R.17, W_R6_VELO.1, W_R_17.1
R_VELO7: J_R7.2, RV_R7.1, SP_R7_2.1, U_R.24, W_R7_VELO.1, W_R_24.1
R_VELO8: J_R8.2, RV_R8.1, SP_R8_2.1, U_R.25, W_R8_VELO.1, W_R_25.1
TFT_CS: J_TFT.6, U_UI.10
TFT_DC: J_TFT.4, U_UI.8
TFT_MISO: J_TFT.8, U_UI.12
TFT_MOSI: J_TFT.7, U_UI.11
TFT_RST: J_TFT.5, U_UI.9
TFT_SCK: J_TFT.1, U_UI.13, W_UI_13.1
TFT_T_CS: J_TFT.2, U_UI.6
TFT_T_IRQ: J_TFT.3, U_UI.7
UART_L_1: U_L.1, U_UI.15, W_L_1.1, W_UI_15.1
UART_L_2: U_L.0, U_UI.14, W_L_0.1, W_UI_14.1
UART_R_1: U_R.1, U_UI.0, W_R_1.1, W_UI_0.1
UART_R_2: U_R.0, U_UI.1, W_R_0.1, W_UI_1.1
UI16: J_ENC_A.10, U_UI.16
UI17: J_ENC_A.9, U_UI.17
UI18: J_ENC_A.8, U_UI.18
UI19: J_ENC_A.7, U_UI.19
UI20: J_ENC_A.6, U_UI.20
UI21: J_ENC_A.5, U_UI.21
UI22: J_ENC_A.4, U_UI.22
UI23: J_ENC_A.3, U_UI.23
UI24: J_ENC_C.1, U_UI.24
UI25: J_ENC_C.2, U_UI.25
UI26: J_ENC_C.3, U_UI.26
UI27: J_ENC_C.4, U_UI.27
UI28: J_ENC_C.5, U_UI.28
UI29: J_ENC_C.6, U_UI.29
UI30: J_ENC_C.7, U_UI.30
UI31: J_ENC_C.8, U_UI.31
UI32: J_ENC_C.9, U_UI.32
UI33: J_ENC_B.9, U_UI.33
UI34: J_ENC_B.8, U_UI.34
UI35: J_ENC_B.7, U_UI.35
UI36: J_ENC_B.6, U_UI.36
UI37: J_ENC_B.5, U_UI.37
UI38: J_ENC_B.4, U_UI.38
UI39: J_ENC_B.3, U_UI.39
UI40: J_ENC_B.2, U_UI.40
UI41: J_ENC_B.1, U_UI.41
